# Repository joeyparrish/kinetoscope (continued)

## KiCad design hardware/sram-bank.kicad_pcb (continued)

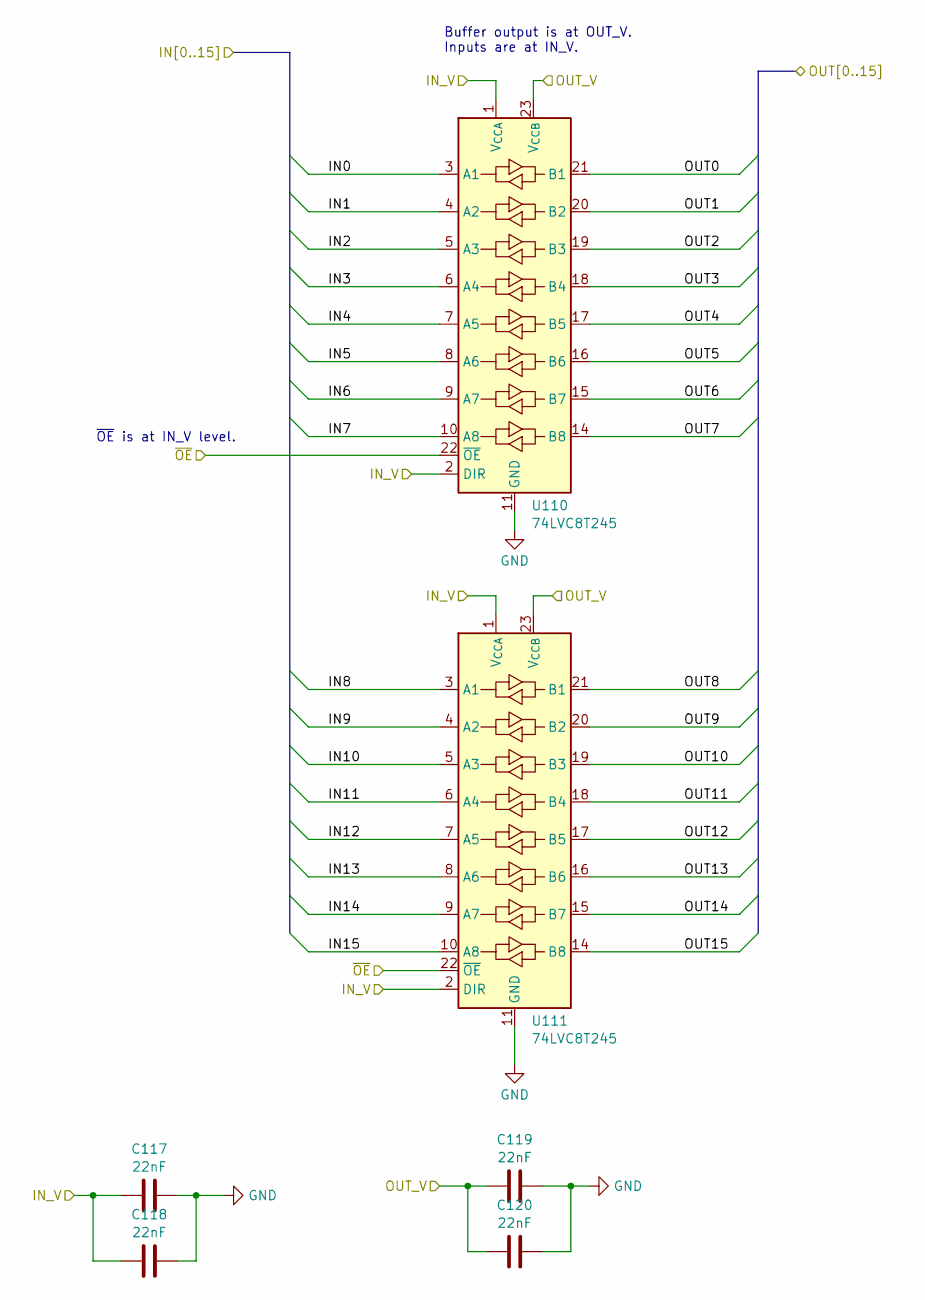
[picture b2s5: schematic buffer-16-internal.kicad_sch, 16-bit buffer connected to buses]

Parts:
C117, C118, C119, C120: 22nF; C_0603_1608Metric; Mouser Part Number 80-C0603C223K4R; JLCPCB Part Number CL10B223KB8NNNC
U110, U111: 74LVC8T245; TSSOP-24_4.4x7.8mm_P0.65mm; Mouser Part Number 595-SN74LVC8T245PWR; JLCPCB Part Number C27643

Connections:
+3.3V: C117.1, C118.1, C119.1, C120.1, U110.1 (V_{CCA}), U110.2 (DIR), U110.23 (V_{CCB}), U110.24 (V_{CCB}), U111.1 (V_{CCA}), U111.2 (DIR), U111.23 (V_{CCB}), U111.24 (V_{CCB}); also elsewhere on the board
/sram-bank-internal/SRAM_DATA0: U110.21 (B1); also elsewhere on the board
/sram-bank-internal/SRAM_DATA1: U110.20 (B2); also elsewhere on the board
/sram-bank-internal/SRAM_DATA2: U110.19 (B3); also elsewhere on the board
/sram-bank-internal/SRAM_DATA3: U110.18 (B4); also elsewhere on the board
/sram-bank-internal/SRAM_DATA4: U110.17 (B5); also elsewhere on the board
/sram-bank-internal/SRAM_DATA5: U110.16 (B6); also elsewhere on the board
/sram-bank-internal/SRAM_DATA6: U110.15 (B7); also elsewhere on the board
/sram-bank-internal/SRAM_DATA7: U110.14 (B8); also elsewhere on the board
/sram-bank-internal/SRAM_DATA8: U111.21 (B1); also elsewhere on the board
/sram-bank-internal/SRAM_DATA9: U111.20 (B2); also elsewhere on the board
/sram-bank-internal/SRAM_DATA10: U111.19 (B3); also elsewhere on the board
/sram-bank-internal/SRAM_DATA11: U111.18 (B4); also elsewhere on the board
/sram-bank-internal/SRAM_DATA12: U111.17 (B5); also elsewhere on the board
/sram-bank-internal/SRAM_DATA13: U111.16 (B6); also elsewhere on the board
/sram-bank-internal/SRAM_DATA14: U111.15 (B7); also elsewhere on the board
/sram-bank-internal/SRAM_DATA15: U111.14 (B8); also elsewhere on the board
/sram-bank-internal/~UC_CONTROL: U110.22 (~OE), U111.22 (~OE); also elsewhere on the board
GND: C117.2, C118.2, C119.2, C120.2, U110.11 (GND), U110.12 (GND), U110.13 (GND), U111.11 (GND), U111.12 (GND), U111.13 (GND); also elsewhere on the board
SRAM_D_IN0: U110.3 (A1); also elsewhere on the board
SRAM_D_IN1: U110.4 (A2); also elsewhere on the board
SRAM_D_IN2: U110.5 (A3); also elsewhere on the board
SRAM_D_IN3: U110.6 (A4); also elsewhere on the board
SRAM_D_IN4: U110.7 (A5); also elsewhere on the board
SRAM_D_IN5: U110.8 (A6); also elsewhere on the board
SRAM_D_IN6: U110.9 (A7); also elsewhere on the board
SRAM_D_IN7: U110.10 (A8); also elsewhere on the board
SRAM_D_IN8: U111.3 (A1); also elsewhere on the board
SRAM_D_IN9: U111.4 (A2); also elsewhere on the board
SRAM_D_IN10: U111.5 (A3); also elsewhere on the board
SRAM_D_IN11: U111.6 (A4); also elsewhere on the board
SRAM_D_IN12: U111.7 (A5); also elsewhere on the board
SRAM_D_IN13: U111.8 (A6); also elsewhere on the board
SRAM_D_IN14: U111.9 (A7); also elsewhere on the board
SRAM_D_IN15: U111.10 (A8); also elsewhere on the board

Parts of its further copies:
C121, C122, C123, C124: 22nF; C_0603_1608Metric; Mouser Part Number 80-C0603C223K4R; JLCPCB Part Number CL10B223KB8NNNC
U112, U113: 74LVC8T245; TSSOP-24_4.4x7.8mm_P0.65mm; Mouser Part Number 595-SN74LVC8T245PWR; JLCPCB Part Number C27643

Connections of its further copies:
+3.3V: C121.1, C122.1, U112.1 (V_{CCA}), U112.2 (DIR), U113.1 (V_{CCA}), U113.2 (DIR); also elsewhere on the board
+5V: C123.1, C124.1, U112.23 (V_{CCB}), U112.24 (V_{CCB}), U113.23 (V_{CCB}), U113.24 (V_{CCB}); also elsewhere on the board
/sram-bank-internal/SRAM_DATA0: U112.3 (A1); also elsewhere on the board
/sram-bank-internal/SRAM_DATA1: U112.4 (A2); also elsewhere on the board
/sram-bank-internal/SRAM_DATA2: U112.5 (A3); also elsewhere on the board
/sram-bank-internal/SRAM_DATA3: U112.6 (A4); also elsewhere on the board
/sram-bank-internal/SRAM_DATA4: U112.7 (A5); also elsewhere on the board
/sram-bank-internal/SRAM_DATA5: U112.8 (A6); also elsewhere on the board
/sram-bank-internal/SRAM_DATA6: U112.9 (A7); also elsewhere on the board
/sram-bank-internal/SRAM_DATA7: U112.10 (A8); also elsewhere on the board
/sram-bank-internal/SRAM_DATA8: U113.3 (A1); also elsewhere on the board
/sram-bank-internal/SRAM_DATA9: U113.4 (A2); also elsewhere on the board
/sram-bank-internal/SRAM_DATA10: U113.5 (A3); also elsewhere on the board
/sram-bank-internal/SRAM_DATA11: U113.6 (A4); also elsewhere on the board
/sram-bank-internal/SRAM_DATA12: U113.7 (A5); also elsewhere on the board
/sram-bank-internal/SRAM_DATA13: U113.8 (A6); also elsewhere on the board
/sram-bank-internal/SRAM_DATA14: U113.9 (A7); also elsewhere on the board
/sram-bank-internal/SRAM_DATA15: U113.10 (A8); also elsewhere on the board
/sram-bank-internal/~SRAM_FINAL_OE: U112.22 (~OE), U113.22 (~OE); also elsewhere on the board
GND: C121.2, C122.2, C123.2, C124.2, U112.11 (GND), U112.12 (GND), U112.13 (GND), U113.11 (GND), U113.12 (GND), U113.13 (GND); also elsewhere on the board
SEGA_D0: U112.21 (B1); also elsewhere on the board
SEGA_D1: U112.20 (B2); also elsewhere on the board
SEGA_D2: U112.19 (B3); also elsewhere on the board
SEGA_D3: U112.18 (B4); also elsewhere on the board
SEGA_D4: U112.17 (B5); also elsewhere on the board
SEGA_D5: U112.16 (B6); also elsewhere on the board
SEGA_D6: U112.15 (B7); also elsewhere on the board
SEGA_D7: U112.14 (B8); also elsewhere on the board
SEGA_D8: U113.21 (B1); also elsewhere on the board
SEGA_D9: U113.20 (B2); also elsewhere on the board
SEGA_D10: U113.19 (B3); also elsewhere on the board
SEGA_D11: U113.18 (B4); also elsewhere on the board
SEGA_D12: U113.17 (B5); also elsewhere on the board
SEGA_D13: U113.16 (B6); also elsewhere on the board
SEGA_D14: U113.15 (B7); also elsewhere on the board
SEGA_D15: U113.14 (B8); also elsewhere on the board

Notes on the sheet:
Buffer output is at OUT_V. Inputs are at IN_V.
~{OE} is at IN_V level.

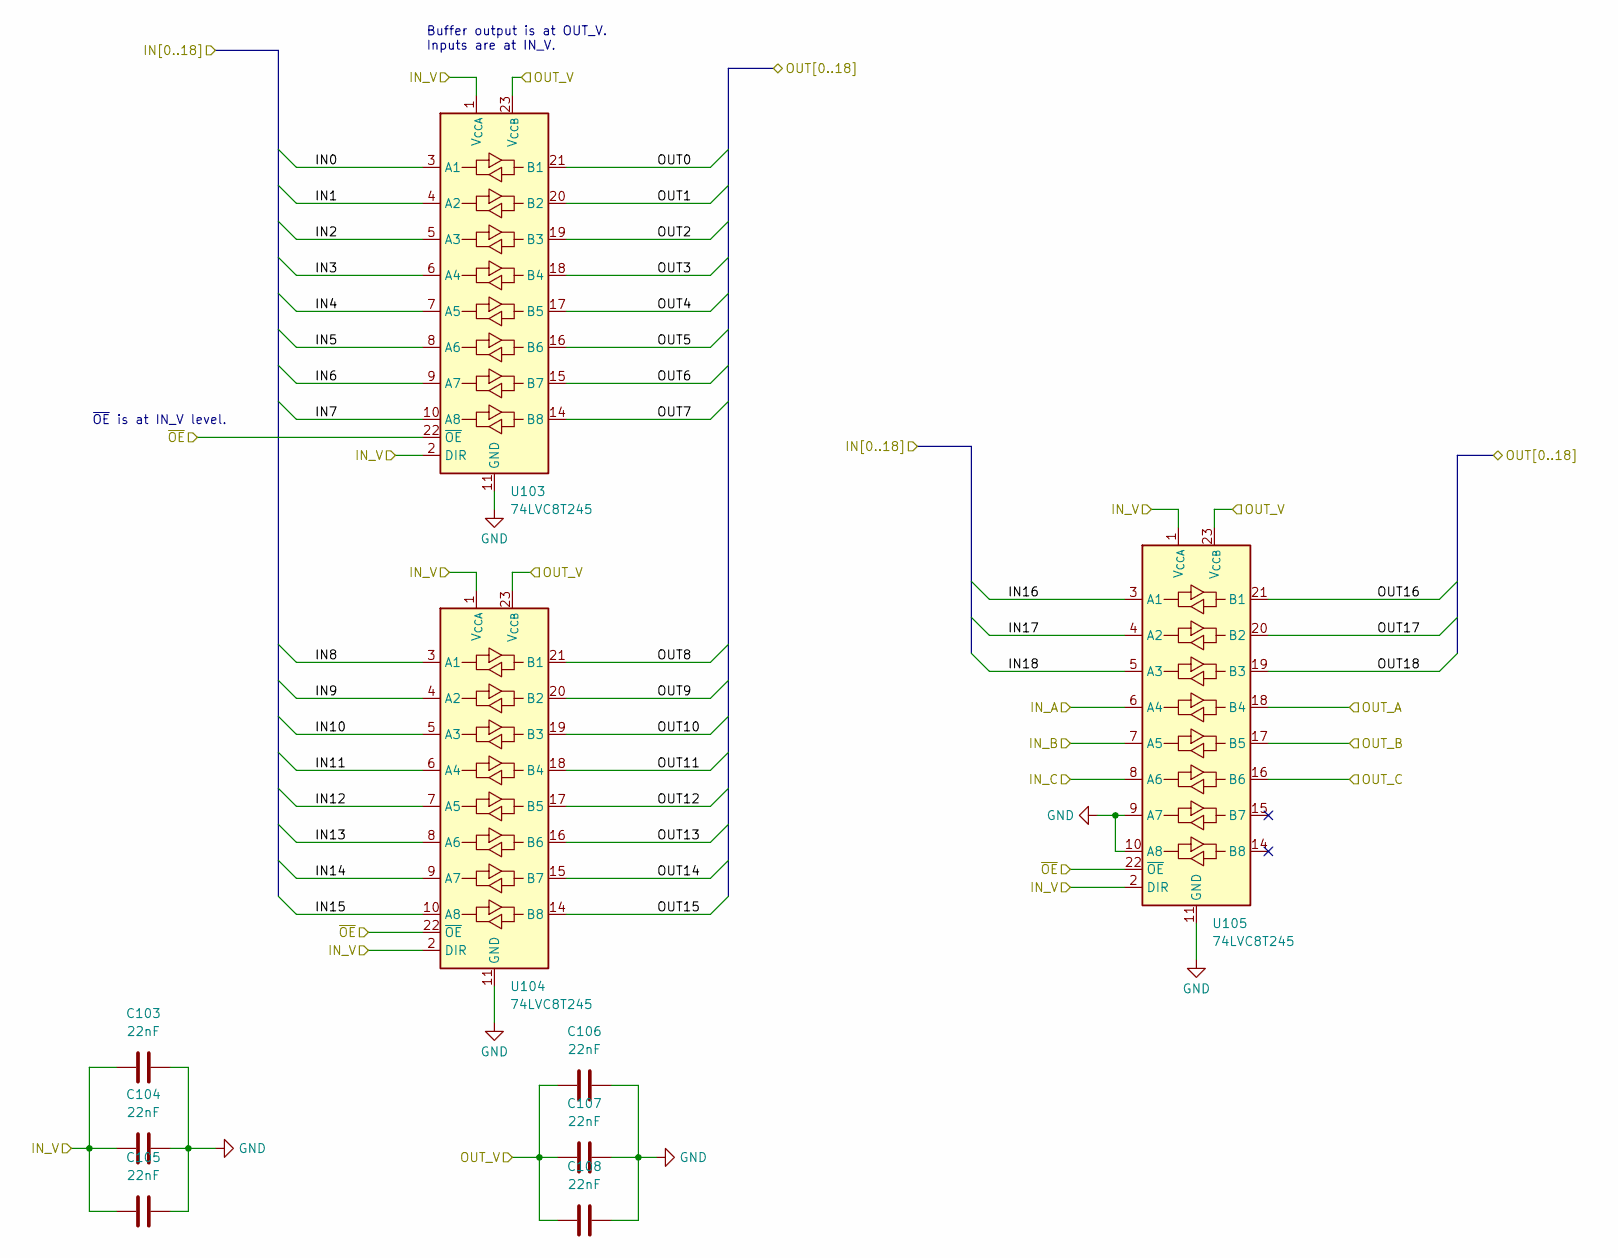
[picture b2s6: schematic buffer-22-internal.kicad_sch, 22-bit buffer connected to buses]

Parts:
C103, C104, C105, C106, C107, C108: 22nF; C_0603_1608Metric; Mouser Part Number 80-C0603C223K4R; JLCPCB Part Number CL10B223KB8NNNC
U103, U104, U105: 74LVC8T245; TSSOP-24_4.4x7.8mm_P0.65mm; Mouser Part Number 595-SN74LVC8T245PWR; JLCPCB Part Number C27643

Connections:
+3.3V: C103.1, C104.1, C105.1, C106.1, C107.1, C108.1, U103.1 (V_{CCA}), U103.2 (DIR), U103.23 (V_{CCB}), U103.24 (V_{CCB}), U104.1 (V_{CCA}), U104.2 (DIR), U104.23 (V_{CCB}), U104.24 (V_{CCB}), U105.1 (V_{CCA}), U105.2 (DIR), U105.8 (A6), U105.23 (V_{CCB}), U105.24 (V_{CCB}); also elsewhere on the board
/sram-bank-internal/SRAM_A0: U103.21 (B1); also elsewhere on the board
/sram-bank-internal/SRAM_A1: U103.20 (B2); also elsewhere on the board
/sram-bank-internal/SRAM_A2: U103.19 (B3); also elsewhere on the board
/sram-bank-internal/SRAM_A3: U103.18 (B4); also elsewhere on the board
/sram-bank-internal/SRAM_A4: U103.17 (B5); also elsewhere on the board
/sram-bank-internal/SRAM_A5: U103.16 (B6); also elsewhere on the board
/sram-bank-internal/SRAM_A6: U103.15 (B7); also elsewhere on the board
/sram-bank-internal/SRAM_A7: U103.14 (B8); also elsewhere on the board
/sram-bank-internal/SRAM_A8: U104.21 (B1); also elsewhere on the board
/sram-bank-internal/SRAM_A9: U104.20 (B2); also elsewhere on the board
/sram-bank-internal/SRAM_A10: U104.19 (B3); also elsewhere on the board
/sram-bank-internal/SRAM_A11: U104.18 (B4); also elsewhere on the board
/sram-bank-internal/SRAM_A12: U104.17 (B5); also elsewhere on the board
/sram-bank-internal/SRAM_A13: U104.16 (B6); also elsewhere on the board
/sram-bank-internal/SRAM_A14: U104.15 (B7); also elsewhere on the board
/sram-bank-internal/SRAM_A15: U104.14 (B8); also elsewhere on the board
/sram-bank-internal/SRAM_A16: U105.21 (B1); also elsewhere on the board
/sram-bank-internal/SRAM_A17: U105.20 (B2); also elsewhere on the board
/sram-bank-internal/SRAM_A18: U105.19 (B3); also elsewhere on the board
/sram-bank-internal/~SEGA_CONTROL: U103.22 (~OE), U104.22 (~OE), U105.22 (~OE); also elsewhere on the board
/sram-bank-internal/~SRAM_FINAL_CE: U105.17 (B5); also elsewhere on the board
/sram-bank-internal/~SRAM_FINAL_OE: U105.18 (B4); also elsewhere on the board
/sram-bank-internal/~SRAM_FINAL_WE: U105.16 (B6); also elsewhere on the board
/sram-bank-internal/~SRAM_OE: U105.6 (A4); also elsewhere on the board
GND: C103.2, C104.2, C105.2, C106.2, C107.2, C108.2, U103.11 (GND), U103.12 (GND), U103.13 (GND), U104.11 (GND), U104.12 (GND), U104.13 (GND), U105.9 (A7), U105.10 (A8), U105.11 (GND), U105.12 (GND), U105.13 (GND); also elsewhere on the board
SEGA_A1: U103.3 (A1); also elsewhere on the board
SEGA_A2: U103.4 (A2); also elsewhere on the board
SEGA_A3: U103.5 (A3); also elsewhere on the board
SEGA_A4: U103.6 (A4); also elsewhere on the board
SEGA_A5: U103.7 (A5); also elsewhere on the board
SEGA_A6: U103.8 (A6); also elsewhere on the board
SEGA_A7: U103.9 (A7); also elsewhere on the board
SEGA_A8: U103.10 (A8); also elsewhere on the board
SEGA_A9: U104.3 (A1); also elsewhere on the board
SEGA_A10: U104.4 (A2); also elsewhere on the board
SEGA_A11: U104.5 (A3); also elsewhere on the board
SEGA_A12: U104.6 (A4); also elsewhere on the board
SEGA_A13: U104.7 (A5); also elsewhere on the board
SEGA_A14: U104.8 (A6); also elsewhere on the board
SEGA_A15: U104.9 (A7); also elsewhere on the board
SEGA_A16: U104.10 (A8); also elsewhere on the board
SEGA_A17: U105.3 (A1); also elsewhere on the board
SEGA_A18: U105.4 (A2); also elsewhere on the board
SEGA_A19: U105.5 (A3); also elsewhere on the board
~SEGA_CE: U105.7 (A5); also elsewhere on the board

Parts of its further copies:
C109, C110, C111, C112, C113, C114: 22nF; C_0603_1608Metric; Mouser Part Number 80-C0603C223K4R; JLCPCB Part Number CL10B223KB8NNNC
U106, U107, U108: 74LVC8T245; TSSOP-24_4.4x7.8mm_P0.65mm; Mouser Part Number 595-SN74LVC8T245PWR; JLCPCB Part Number C27643

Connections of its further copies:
+3.3V: C109.1, C110.1, C111.1, C112.1, C113.1, C114.1, U106.1 (V_{CCA}), U106.2 (DIR), U106.23 (V_{CCB}), U106.24 (V_{CCB}), U107.1 (V_{CCA}), U107.2 (DIR), U107.23 (V_{CCB}), U107.24 (V_{CCB}), U108.1 (V_{CCA}), U108.2 (DIR), U108.6 (A4), U108.23 (V_{CCB}), U108.24 (V_{CCB}); also elsewhere on the board
/sram-bank-internal/SRAM_A0: U106.21 (B1); also elsewhere on the board
/sram-bank-internal/SRAM_A1: U106.20 (B2); also elsewhere on the board
/sram-bank-internal/SRAM_A2: U106.19 (B3); also elsewhere on the board
/sram-bank-internal/SRAM_A3: U106.18 (B4); also elsewhere on the board
/sram-bank-internal/SRAM_A4: U106.17 (B5); also elsewhere on the board
/sram-bank-internal/SRAM_A5: U106.16 (B6); also elsewhere on the board
/sram-bank-internal/SRAM_A6: U106.15 (B7); also elsewhere on the board
/sram-bank-internal/SRAM_A7: U106.14 (B8); also elsewhere on the board
/sram-bank-internal/SRAM_A8: U107.21 (B1); also elsewhere on the board
/sram-bank-internal/SRAM_A9: U107.20 (B2); also elsewhere on the board
/sram-bank-internal/SRAM_A10: U107.19 (B3); also elsewhere on the board
/sram-bank-internal/SRAM_A11: U107.18 (B4); also elsewhere on the board
/sram-bank-internal/SRAM_A12: U107.17 (B5); also elsewhere on the board
/sram-bank-internal/SRAM_A13: U107.16 (B6); also elsewhere on the board
/sram-bank-internal/SRAM_A14: U107.15 (B7); also elsewhere on the board
/sram-bank-internal/SRAM_A15: U107.14 (B8); also elsewhere on the board
/sram-bank-internal/SRAM_A16: U108.21 (B1); also elsewhere on the board
/sram-bank-internal/SRAM_A17: U108.20 (B2); also elsewhere on the board
/sram-bank-internal/SRAM_A18: U108.19 (B3); also elsewhere on the board
/sram-bank-internal/~SRAM_FINAL_CE: U108.17 (B5); also elsewhere on the board
/sram-bank-internal/~SRAM_FINAL_OE: U108.18 (B4); also elsewhere on the board
/sram-bank-internal/~SRAM_FINAL_WE: U108.16 (B6); also elsewhere on the board
/sram-bank-internal/~UC_CONTROL: U106.22 (~OE), U107.22 (~OE), U108.22 (~OE); also elsewhere on the board
GND: C109.2, C110.2, C111.2, C112.2, C113.2, C114.2, U106.11 (GND), U106.12 (GND), U106.13 (GND), U107.11 (GND), U107.12 (GND), U107.13 (GND), U108.9 (A7), U108.10 (A8), U108.11 (GND), U108.12 (GND), U108.13 (GND); also elsewhere on the board
SRAM_W_A0: U106.3 (A1); also elsewhere on the board
SRAM_W_A1: U106.4 (A2); also elsewhere on the board
SRAM_W_A2: U106.5 (A3); also elsewhere on the board
SRAM_W_A3: U106.6 (A4); also elsewhere on the board
SRAM_W_A4: U106.7 (A5); also elsewhere on the board
SRAM_W_A5: U106.8 (A6); also elsewhere on the board
SRAM_W_A6: U106.9 (A7); also elsewhere on the board
SRAM_W_A7: U106.10 (A8); also elsewhere on the board
SRAM_W_A8: U107.3 (A1); also elsewhere on the board
SRAM_W_A9: U107.4 (A2); also elsewhere on the board
SRAM_W_A10: U107.5 (A3); also elsewhere on the board
SRAM_W_A11: U107.6 (A4); also elsewhere on the board
SRAM_W_A12: U107.7 (A5); also elsewhere on the board
SRAM_W_A13: U107.8 (A6); also elsewhere on the board
SRAM_W_A14: U107.9 (A7); also elsewhere on the board
SRAM_W_A15: U107.10 (A8); also elsewhere on the board
SRAM_W_A16: U108.3 (A1); also elsewhere on the board
SRAM_W_A17: U108.4 (A2); also elsewhere on the board
SRAM_W_A18: U108.5 (A3); also elsewhere on the board
~SRAM_WE: U108.7 (A5), U108.8 (A6); also elsewhere on the board

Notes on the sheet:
~{OE} is at IN_V level.
Buffer output is at OUT_V. Inputs are at IN_V.

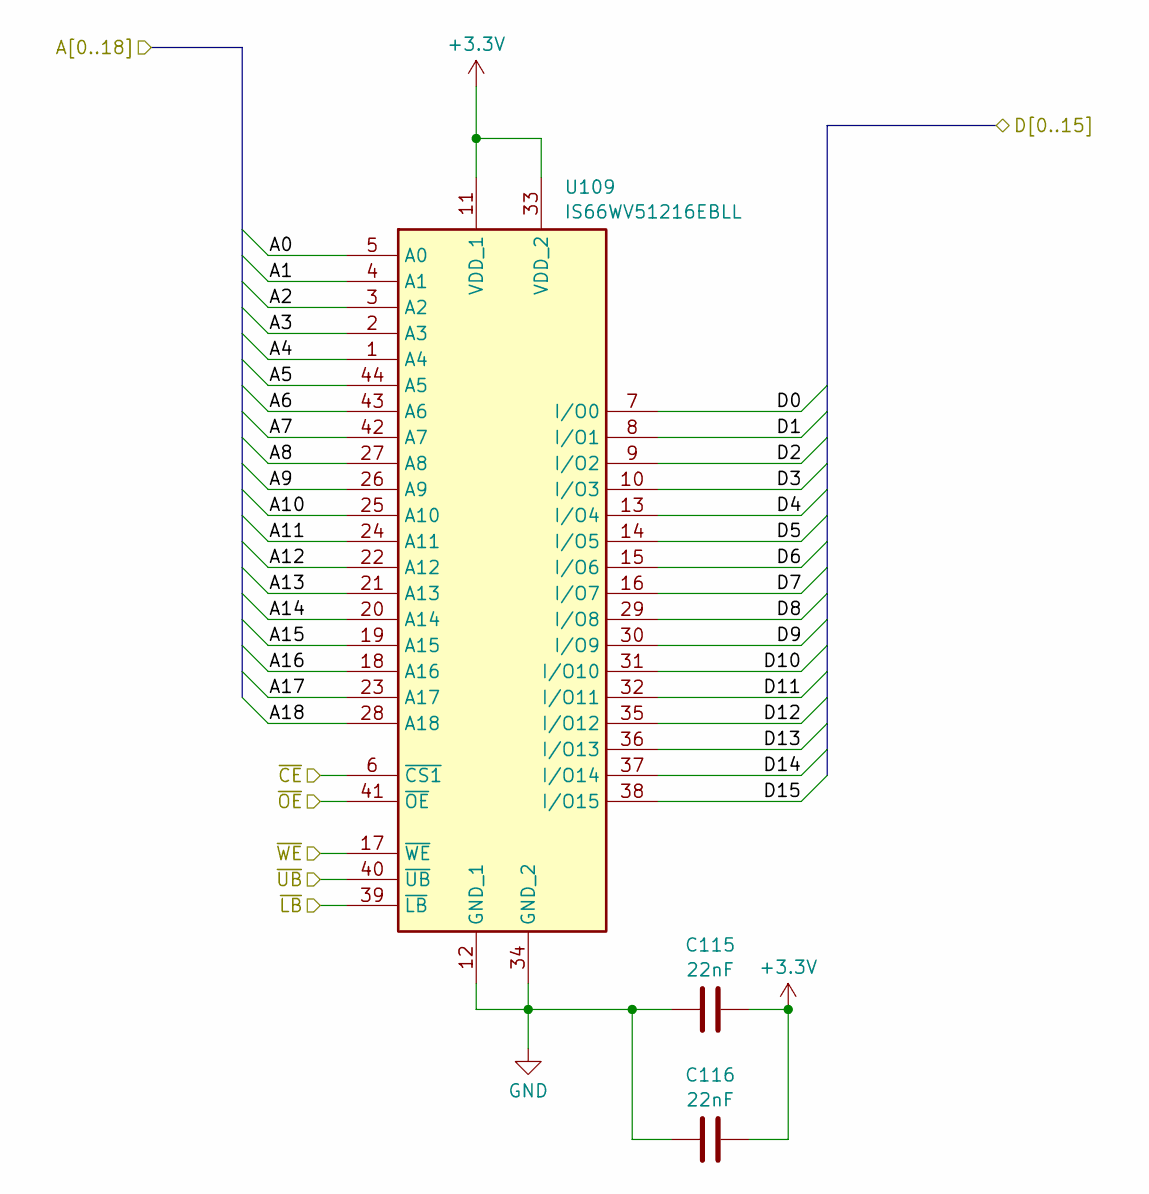
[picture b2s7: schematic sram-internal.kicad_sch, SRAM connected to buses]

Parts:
C115, C116: 22nF; C_0603_1608Metric; Mouser Part Number 80-C0603C223K4R; JLCPCB Part Number CL10B223KB8NNNC
U109: IS66WV51216EBLL; TSOP-II-44_10.16x18.41mm_P0.8mm; Mouser Part Number 870-66WV512EBLL55TLI

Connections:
+3.3V: C115.2, C116.2, U109.11 (VDD_1), U109.33 (VDD_2); also elsewhere on the board
/sram-bank-internal/SRAM_A0: U109.5 (A0); also elsewhere on the board
/sram-bank-internal/SRAM_A1: U109.4 (A1); also elsewhere on the board
/sram-bank-internal/SRAM_A2: U109.3 (A2); also elsewhere on the board
/sram-bank-internal/SRAM_A3: U109.2 (A3); also elsewhere on the board
/sram-bank-internal/SRAM_A4: U109.1 (A4); also elsewhere on the board
/sram-bank-internal/SRAM_A5: U109.44 (A5); also elsewhere on the board
/sram-bank-internal/SRAM_A6: U109.43 (A6); also elsewhere on the board
/sram-bank-internal/SRAM_A7: U109.42 (A7); also elsewhere on the board
/sram-bank-internal/SRAM_A8: U109.27 (A8); also elsewhere on the board
/sram-bank-internal/SRAM_A9: U109.26 (A9); also elsewhere on the board
/sram-bank-internal/SRAM_A10: U109.25 (A10); also elsewhere on the board
/sram-bank-internal/SRAM_A11: U109.24 (A11); also elsewhere on the board
/sram-bank-internal/SRAM_A12: U109.22 (A12); also elsewhere on the board
/sram-bank-internal/SRAM_A13: U109.21 (A13); also elsewhere on the board
/sram-bank-internal/SRAM_A14: U109.20 (A14); also elsewhere on the board
/sram-bank-internal/SRAM_A15: U109.19 (A15); also elsewhere on the board
/sram-bank-internal/SRAM_A16: U109.18 (A16); also elsewhere on the board
/sram-bank-internal/SRAM_A17: U109.23 (A17); also elsewhere on the board
/sram-bank-internal/SRAM_A18: U109.28 (A18); also elsewhere on the board
/sram-bank-internal/SRAM_DATA0: U109.7 (I/O0); also elsewhere on the board
/sram-bank-internal/SRAM_DATA1: U109.8 (I/O1); also elsewhere on the board
/sram-bank-internal/SRAM_DATA2: U109.9 (I/O2); also elsewhere on the board
/sram-bank-internal/SRAM_DATA3: U109.10 (I/O3); also elsewhere on the board
/sram-bank-internal/SRAM_DATA4: U109.13 (I/O4); also elsewhere on the board
/sram-bank-internal/SRAM_DATA5: U109.14 (I/O5); also elsewhere on the board
/sram-bank-internal/SRAM_DATA6: U109.15 (I/O6); also elsewhere on the board
/sram-bank-internal/SRAM_DATA7: U109.16 (I/O7); also elsewhere on the board
/sram-bank-internal/SRAM_DATA8: U109.29 (I/O8); also elsewhere on the board
/sram-bank-internal/SRAM_DATA9: U109.30 (I/O9); also elsewhere on the board
/sram-bank-internal/SRAM_DATA10: U109.31 (I/O10); also elsewhere on the board
/sram-bank-internal/SRAM_DATA11: U109.32 (I/O11); also elsewhere on the board
/sram-bank-internal/SRAM_DATA12: U109.35 (I/O12); also elsewhere on the board
/sram-bank-internal/SRAM_DATA13: U109.36 (I/O13); also elsewhere on the board
/sram-bank-internal/SRAM_DATA14: U109.37 (I/O14); also elsewhere on the board
/sram-bank-internal/SRAM_DATA15: U109.38 (I/O15); also elsewhere on the board
/sram-bank-internal/~SRAM_FINAL_CE: U109.6 (~CS1); also elsewhere on the board
/sram-bank-internal/~SRAM_FINAL_OE: U109.41 (~OE); also elsewhere on the board
/sram-bank-internal/~SRAM_FINAL_WE: U109.17 (~WE); also elsewhere on the board
GND: C115.1, C116.1, U109.12 (GND_1), U109.34 (GND_2), U109.39 (~LB), U109.40 (~UB); also elsewhere on the board

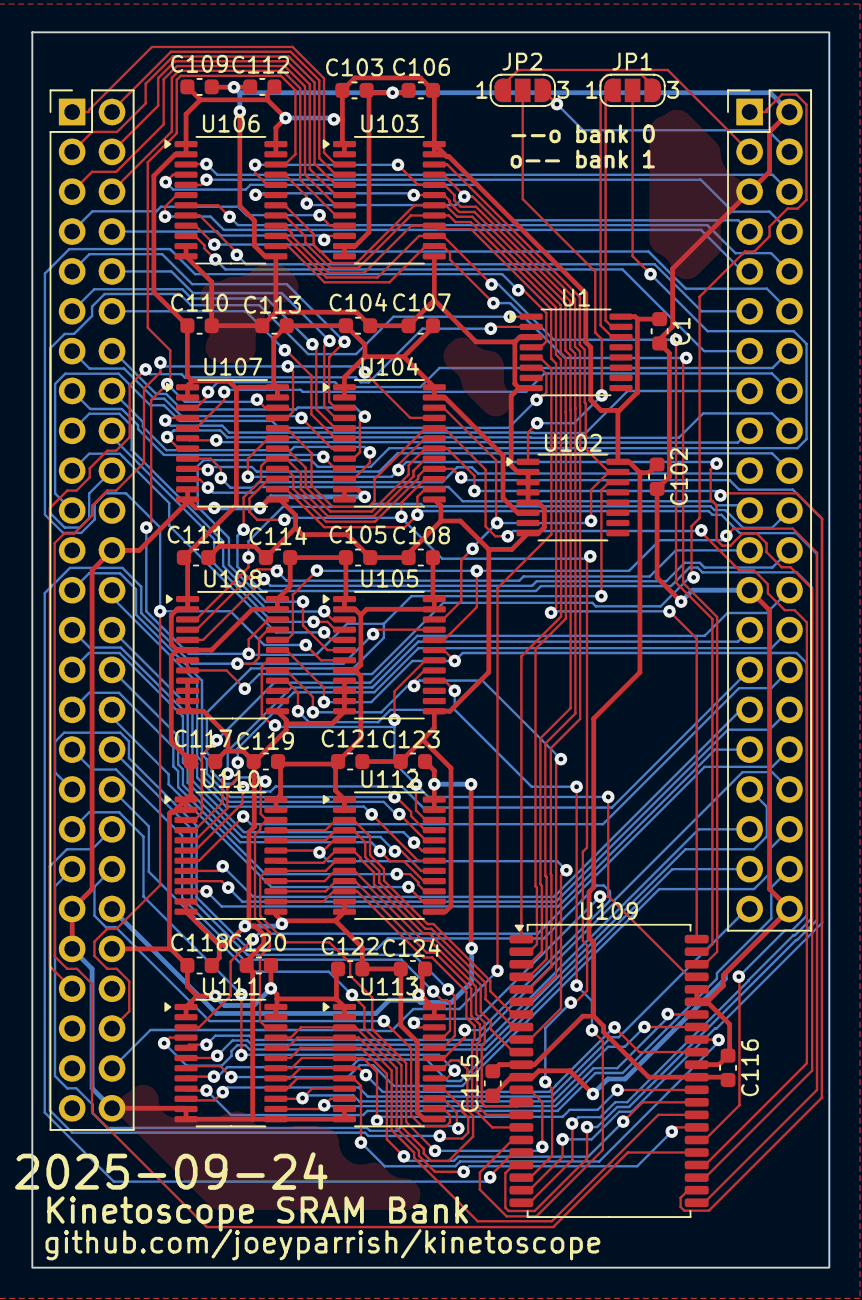
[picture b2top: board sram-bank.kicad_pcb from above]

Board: 2 copper layers, 50.8 x 78.7 mm, 42 parts (0 on the bottom side), 125 nets.

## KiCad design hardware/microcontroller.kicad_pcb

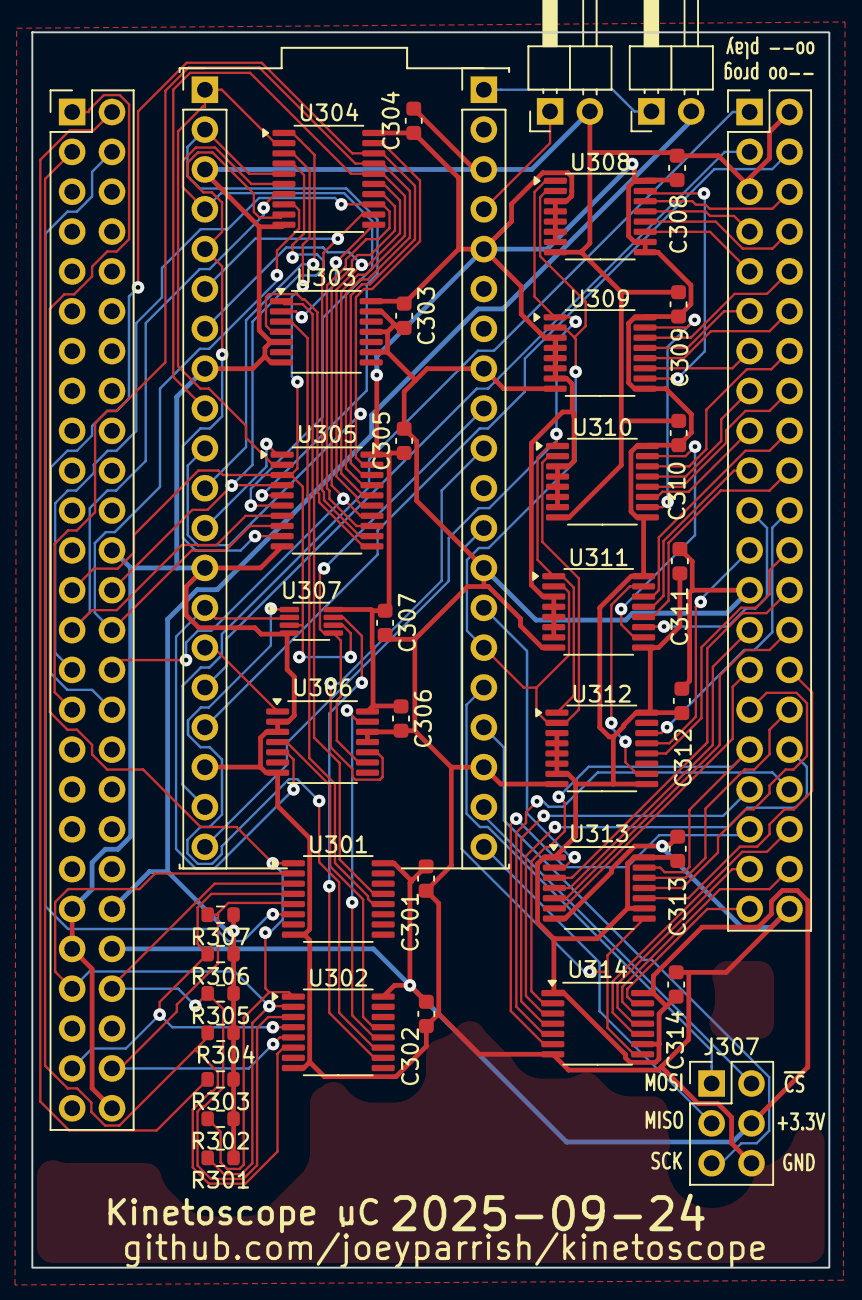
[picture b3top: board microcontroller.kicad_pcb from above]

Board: 2 copper layers, 50.8 x 78.7 mm, 44 parts (0 on the bottom side), 93 nets.

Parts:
C301, C302, C303, C304, C305, C306, C307, C308, C309, C310, C311, C312, C313, C314: 22nF; C_0603_1608Metric
J301: PinHeader_2x26_P2.54mm_Vertical
J302: PinHeader_2x21_P2.54mm_Vertical
J303, J304: PinHeader_1x20_P2.54mm_Vertical
J305, J306: 1x2 jumper right-angle; PinHeader_1x02_P2.54mm_Horizontal
J307: Conn_02x03_Odd_Even; PinHeader_2x03_P2.54mm_Vertical
R301, R302, R303, R304, R305, R306, R307: 10k; R_0603_1608Metric
U301, U302: 74LVC138A; TSSOP-16_4.4x5mm_P0.65mm
U303: 74AHC04; TSSOP-14_4.4x5mm_P0.65mm
U304, U305: 74AHC373; TSSOP-20_4.4x6.5mm_P0.65mm
U306: 74AHC74; TSSOP-14_4.4x5mm_P0.65mm
U307: 74LVC2G125; VSSOP-8_2.3x2mm_P0.5mm
U308, U309, U310, U311, U312: 74LV161A; TSSOP-16_4.4x5mm_P0.65mm
U313, U314: 74LV164A; TSSOP-14_4.4x5mm_P0.65mm
X301: kinetoscope-cart-board-template
X302: Raspberry_Pi_Pico_W_template

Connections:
+3.3V: C301.1, C302.1, C303.1, C304.1, C305.1, C306.1, C307.1, C308.1, C309.1, C310.1, C311.1, C312.1, C313.1, C314.1, J301.44 (3V), J304.5 (3V3_Out), J307.4, U301.16 (VCC), U302.16 (VCC), U303.14 (VCC), U304.20 (VCC), U305.20 (VCC), U306.14 (VCC), U307.8 (VCC), U308.3 (D0), U308.4 (D1), U308.5 (D2), U308.6 (D3), U308.7 (CEP), U308.9 (~PE), U308.10 (CET), U308.16 (VCC), U309.3 (D0), U309.4 (D1), U309.5 (D2), U309.6 (D3), U309.7 (CEP), U309.9 (~PE), U309.16 (VCC), U310.3 (D0), U310.4 (D1), U310.5 (D2), U310.6 (D3), U310.7 (CEP), U310.9 (~PE), U310.16 (VCC), U311.3 (D0), U311.4 (D1), U311.5 (D2), U311.6 (D3), U311.7 (CEP), U311.9 (~PE), U311.16 (VCC), U312.3 (D0), U312.4 (D1), U312.5 (D2), U312.6 (D3), U312.7 (CEP), U312.9 (~PE), U312.16 (VCC), U313.1 (DSA), U313.9 (~MR), U313.14 (VCC), U314.1 (DSA), U314.9 (~MR), U314.14 (VCC)
+5V: J301.42 (5V), J305.2 (B), R301.1, R302.1, R303.1, R304.1, R305.1, R306.1, R307.1
/microcontroller-internal/CMD_3V: J303.14 (GP10), U306.5 (Q), U307.2
/microcontroller-internal/ERR_3V: J304.9 (GP27/A1), U306.9 (Q), U307.5
/microcontroller-internal/REG_EN: J304.4 (3V3_En), J306.1 (A)
/microcontroller-internal/REG_R_D0: J303.1 (GP0), U304.2 (O0), U305.2 (O0)
/microcontroller-internal/REG_R_D1: J303.2 (GP1), U304.5 (O1), U305.5 (O1)
/microcontroller-internal/REG_R_D2: J303.4 (GP2), U304.6 (O2), U305.6 (O2)
/microcontroller-internal/REG_R_D3: J303.5 (GP3), U304.9 (O3), U305.9 (O3)
/microcontroller-internal/REG_R_D4: J303.6 (GP4), U304.12 (O4), U305.12 (O4)
/microcontroller-internal/REG_R_D5: J303.7 (GP5), U304.15 (O5), U305.15 (O5)
/microcontroller-internal/REG_R_D6: J303.9 (GP6), U304.16 (O6), U305.16 (O6)
/microcontroller-internal/REG_R_D7: J303.10 (GP7), U304.19 (O7), U305.19 (O7)
/microcontroller-internal/SPI_MISO: J304.20 (GP16), J307.3
/microcontroller-internal/SPI_MOSI: J304.16 (GP19), J307.1
/microcontroller-internal/SPI_SCK: J304.17 (GP18), J307.5
/microcontroller-internal/VBUS: J304.1 (VBUS), J305.1 (A)
/microcontroller-internal/address-counter-internal/AR0: U308.15 (TC), U309.10 (CET)
/microcontroller-internal/address-counter-internal/AR1: U309.15 (TC), U310.10 (CET)
/microcontroller-internal/address-counter-internal/AR2: U310.15 (TC), U311.10 (CET)
/microcontroller-internal/address-counter-internal/AR3: U311.15 (TC), U312.10 (CET)
/microcontroller-internal/register-file-internal/REG_0_WE: U303.2, U304.11 (LE)
/microcontroller-internal/register-file-internal/REG_1_WE: U303.4, U305.11 (LE)
/microcontroller-internal/~CMD_CLR: J303.15 (GP11), U306.1 (~R)
/microcontroller-internal/~CMD_OE: U302.11 (~Y4), U307.1
/microcontroller-internal/~CMD_SET: U302.13 (~Y2), U306.4 (~S)
/microcontroller-internal/~ERR_CLR: U302.12 (~Y3), U306.13 (~R)
/microcontroller-internal/~ERR_OE: U302.10 (~Y5), U307.7
/microcontroller-internal/~ERR_SET: J304.10 (GP26/A0), U306.10 (~S)
/microcontroller-internal/~REG_0_OE: J303.11 (GP8), U304.1 (OE)
/microcontroller-internal/~REG_0_WE: U301.13 (~Y2), U303.1
/microcontroller-internal/~REG_1_OE: J303.12 (GP9), U305.1 (OE)
/microcontroller-internal/~REG_1_WE: U301.12 (~Y3), U303.3
/microcontroller-internal/~SPI_CS: J304.19 (GP17), J307.2
GND: C301.2, C302.2, C303.2, C304.2, C305.2, C306.2, C307.2, C308.2, C309.2, C310.2, C311.2, C312.2, C313.2, C314.2, J301.24 (GND), J301.41 (GND), J301.43 (GND), J301.52 (GND), J302.2 (GND), J302.5 (GND), J302.25 (GND), J302.42 (GND), J303.3 (GND), J303.8 (GND), J303.13 (GND), J303.18 (GND), J304.3 (GND), J304.8 (ADC_GND), J304.13 (GND), J304.18 (GND), J306.2 (B), J307.6, U301.8 (GND), U302.8 (GND), U303.5, U303.7 (GND), U303.9, U303.11, U303.13, U304.10 (GND), U305.10 (GND), U306.2 (D), U306.3 (C), U306.7 (GND), U306.11 (C), U306.12 (D), U307.4 (GND), U308.8 (GND), U309.8 (GND), U310.8 (GND), U311.8 (GND), U312.8 (GND), U313.7 (GND), U314.7 (GND)
SEGA_A1: J301.1 (SEGA_A1), R302.2, U301.1 (A0), U302.1 (A0)
SEGA_A2: J301.2 (SEGA_A2), R303.2
SEGA_A3: J301.3 (SEGA_A3), R304.2, U302.6 (E2)
SEGA_A4: J301.4 (SEGA_A4), U301.6 (E2)
SEGA_D0: J301.25 (SEGA_D0), U304.3 (D0), U305.3 (D0), U307.3, U307.6
SEGA_D1: J301.26 (SEGA_D1), U304.4 (D1), U305.4 (D1)
SEGA_D2: J301.27 (SEGA_D2), U304.7 (D2), U305.7 (D2)
SEGA_D3: J301.28 (SEGA_D3), U304.8 (D3), U305.8 (D3)
SEGA_D4: J301.29 (SEGA_D4), U304.13 (D4), U305.13 (D4)
SEGA_D5: J301.30 (SEGA_D5), U304.14 (D5), U305.14 (D5)
SEGA_D6: J301.31 (SEGA_D6), U304.17 (D6), U305.17 (D6)
SEGA_D7: J301.32 (SEGA_D7), U304.18 (D7), U305.18 (D7)
SRAM_DIS_0: J302.3 (SRAM_DIS_0), J303.16 (GP12)
SRAM_DIS_1: J302.4 (SRAM_DIS_1), J303.17 (GP13)
SRAM_D_CLK: J304.12 (GP22), U313.8 (CP), U314.8 (CP)
SRAM_D_IN0: J302.26 (SRAM_D_IN0), U313.3 (Q0)
SRAM_D_IN1: J302.27 (SRAM_D_IN1), U313.4 (Q1)
SRAM_D_IN2: J302.28 (SRAM_D_IN2), U313.5 (Q2)
SRAM_D_IN3: J302.29 (SRAM_D_IN3), U313.6 (Q3)
SRAM_D_IN4: J302.30 (SRAM_D_IN4), U313.10 (Q4)
SRAM_D_IN5: J302.31 (SRAM_D_IN5), U313.11 (Q5)
SRAM_D_IN6: J302.32 (SRAM_D_IN6), U313.12 (Q6)
SRAM_D_IN7: J302.33 (SRAM_D_IN7), U313.13 (Q7), U314.2 (DSB)
SRAM_D_IN8: J302.34 (SRAM_D_IN8), U314.3 (Q0)
SRAM_D_IN9: J302.35 (SRAM_D_IN9), U314.4 (Q1)
SRAM_D_IN10: J302.36 (SRAM_D_IN10), U314.5 (Q2)
SRAM_D_IN11: J302.37 (SRAM_D_IN11), U314.6 (Q3)
SRAM_D_IN12: J302.38 (SRAM_D_IN12), U314.10 (Q4)
SRAM_D_IN13: J302.39 (SRAM_D_IN13), U314.11 (Q5)
SRAM_D_IN14: J302.40 (SRAM_D_IN14), U314.12 (Q6)
SRAM_D_IN15: J302.41 (SRAM_D_IN15), U314.13 (Q7)
SRAM_D_NEXT: J304.14 (GP21), U313.2 (DSB)
SRAM_W_A0: J302.6 (SRAM_W_A0), U308.14 (Q0)
SRAM_W_A1: J302.7 (SRAM_W_A1), U308.13 (Q1)
SRAM_W_A2: J302.8 (SRAM_W_A2), U308.12 (Q2)
SRAM_W_A3: J302.9 (SRAM_W_A3), U308.11 (Q3)
SRAM_W_A4: J302.10 (SRAM_W_A4), U309.14 (Q0)
SRAM_W_A5: J302.11 (SRAM_W_A5), U309.13 (Q1)
SRAM_W_A6: J302.12 (SRAM_W_A6), U309.12 (Q2)
SRAM_W_A7: J302.13 (SRAM_W_A7), U309.11 (Q3)
SRAM_W_A8: J302.14 (SRAM_W_A8), U310.14 (Q0)
SRAM_W_A9: J302.15 (SRAM_W_A9), U310.13 (Q1)
SRAM_W_A10: J302.16 (SRAM_W_A10), U310.12 (Q2)
SRAM_W_A11: J302.17 (SRAM_W_A11), U310.11 (Q3)
SRAM_W_A12: J302.18 (SRAM_W_A12), U311.14 (Q0)
SRAM_W_A13: J302.19 (SRAM_W_A13), U311.13 (Q1)
SRAM_W_A14: J302.20 (SRAM_W_A14), U311.12 (Q2)
SRAM_W_A15: J302.21 (SRAM_W_A15), U311.11 (Q3)
SRAM_W_A16: J302.22 (SRAM_W_A16), U312.14 (Q0)
SRAM_W_A17: J302.23 (SRAM_W_A17), U312.13 (Q1)
SRAM_W_A18: J302.24 (SRAM_W_A18), U312.12 (Q2)
SRAM_W_A_CLK: J304.15 (GP20), U308.2 (CP), U309.2 (CP), U310.2 (CP), U311.2 (CP), U312.2 (CP)
~SEGA_AS: J301.50 (~SEGA_AS), R307.2, U301.5 (~E1), U302.5 (~E1)
~SEGA_OE: J301.45 (~SEGA_OE), R301.2, U301.2 (A1), U302.2 (A1)
~SEGA_REGISTER: J301.49 (~SEGA_REGISTER), R306.2, U301.4 (~E0), U302.4 (~E0)
~SEGA_WE_LB: J301.46 (~SEGA_WE_LB), R305.2, U301.3 (A2), U302.3 (A2)
~SRAM_WE: J302.1 (~SRAM_WE), J303.19 (GP14)
~SRAM_W_A_CLR: J303.20 (GP15), U308.1 (~MR), U309.1 (~MR), U310.1 (~MR), U311.1 (~MR), U312.1 (~MR)

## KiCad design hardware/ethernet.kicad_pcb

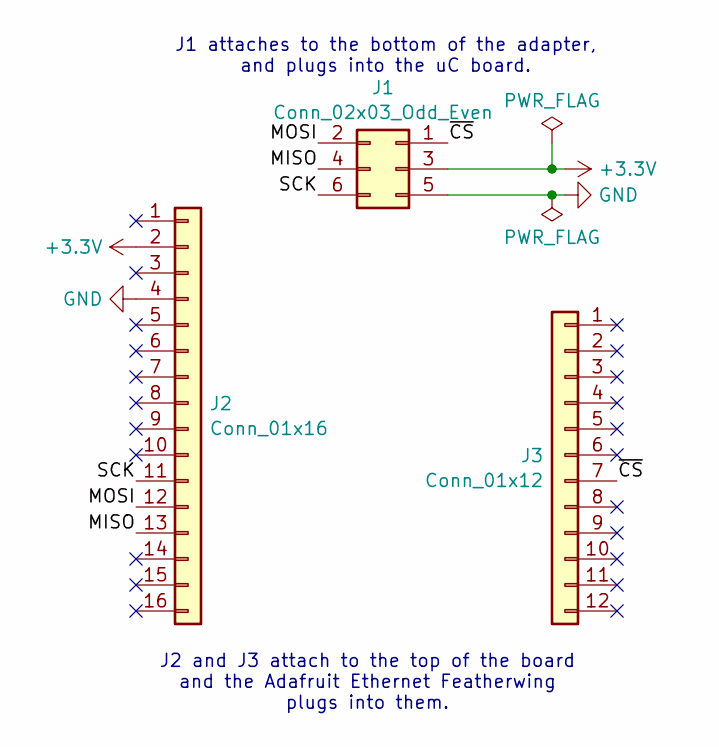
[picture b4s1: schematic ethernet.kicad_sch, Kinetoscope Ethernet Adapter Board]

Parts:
J1: Conn_02x03_Odd_Even; PinHeader_2x03_P2.54mm_Vertical; Mouser Part Number 737-PH2-06-UA; JLCPCB Part Number C7501594
J2: Conn_01x16; PinHeader_1x16_P2.54mm_Vertical; Mouser Part Number 710-61301611821; JLCPCB Part Number C18078137
J3: Conn_01x12; PinHeader_1x12_P2.54mm_Vertical; Mouser Part Number 710-61301211821; JLCPCB Part Number C7499331

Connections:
+3.3V: J1.3, J2.2
/MISO: J1.4, J2.13
/MOSI: J1.2, J2.12
/SCK: J1.6, J2.11
/~CS: J1.1, J3.7
GND: J1.5, J2.4

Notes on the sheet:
J1 attaches to the bottom of the adapter, and plugs into the uC board.
J2 and J3 attach to the top of the board and the Adafruit Ethernet Featherwing plugs into them.
